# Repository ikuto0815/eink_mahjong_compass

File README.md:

# E-ink mahjong compass

This repo contains all the files neccesary to build a bluetooth controlled digital mahjong compass.

The project is divided into the following main parts:

* [**3d**](3d): the freecad project and stl-files to 3D print the case
* [**android_app**](android_app): the android app used to control the device
* [**firmware**](firmware): firmware for the ESP32 microcontroller inside
* [**pcb**](pcb): design files for the custom PCB

Additional folders:

* [**fontconvert**](fontconvert): tool to convert fonts to C headers, so they can be used in the firmware
* [**hardware**](hardware): datasheets for parts used on the PCB

## PCB

The custom made PCB contains an ESP32-S3-WROOM1 microcontroller to talk to a phone via bluetooth and control the connected periphery.

It has the following components:

* 4.2 inch 400x300 (300x300 visible) E-ink display
* 4 buttons for controlling the device
* 4 indicator LEDs placed below the riichi bet trays of each player
* USB-C port for programming the ESP32 and charging the battery
* TP4056 module to control charging of a single cell LiPo battery via the USB-C port
* (optional and untested MAX17048 fuel gauge controller to determine the battery charge)

The production subfolder contains all the files needed to order the PCBs.
The `eink_mahjong_compass.zip` file contains alle the gerber files needed to order the PCB.
`bom.csv` and `positions.csv` are additionally needed when ordering the PCBs assembled.
The files for assembly will work for JLCPCB, other sites might need a different file format.

Even when ordering with assembly, two parts have to be soldered by hand. Those being the connector
for the E-ink display and the ESP32 module. Adding those would make the assembly service much more expensive.

## How to build

### Requirements

The following things need to be ordered:

* WeAct 4.2 inch Epaper module <https://aliexpress.com/item/1005008461198386.html> (only sold by WeAct Studio Official Store, order the black/white one, the black/red/white variant might not work)
* ESP32-S3-WROOM1-N4 <https://aliexpress.com/item/1005004815894336.html> (there are various vendors, they should all be fine. -N4 is the cheapest variant with 4MB flash and no external RAM. The better variants will probably work as well but won't provide any benefits)
* 2x 4 pin PCB Female Pin Header Socket Connector <https://aliexpress.com/item/1005004122312694.html> for the display connector
* (optional) Ntag 215 NFC tag stickers <https://aliexpress.com/item/1005006387440192.html> stick them on the underside of the lid and write the connect URL to them, so the app auto starts when touching item
* battery, either a 5000mAh 105080 or a 6000mAh 906090 can be used, other formats would need changes to the 3D printed part to hold the battery in place. Example seller <https://aliexpress.com/item/1005004639603622.html> batteries from other sellers will probably work fine as well, but a 2 pin connector is required, not a 3 pin one.
* M3xL4xOD4.2 brass insert nuts. <https://de.aliexpress.com/item/1005006472702418.html> Molded into the case to hold the lid screws
* M3 6mm countersunk screws <https://aliexpress.com/item/33006942612.html>

### Assembly

* 3D print the parts as described in [3d/README](3d/README.md).
* Using a soldering iron push the brass insert nuts into the corners of the case.
* Place the PCB on the printed `display_feet`
* Place the display_feet on top
* Put them into the case
* Place the battery inside and connect it after checking if the polarity of the connector matches that on the PCB.
* Add the screen
* Place the lid on top and screw it down.

### Flashing the firmware

To build and flash the firmware, you need to download and install  [PlatformIO](https://platformio.org/).

Then just connect the compass via USB and run `pio run --target upload` in the firmware directory.

## Other stuff

### Bluetooth interface

The compass currently offers a single BLE service under the UID `bae5e4dd-f2b4-4461-a84c-b7851fb8efd3` with the following characteristics:

#### game state (`bab40271-33ea-48dc-a145-638361f54d2b`)

This characteristic is write only and takes a multi line string that describes the current game state in the following format:

``` text
roundIndex riichiCount honbaCount
windIndex0
score0
name0
windIndex1
score1
name1
windIndex2
score2
name2
windIndex3
score3
name3
```

roundIndex describes the current round of the game (0=E1, 1=E2, 4=S1,...). riichiCount and honbaCount are the number of sticks that would be on the table.

The next lines describe describe the 4 players in the game.
windIndexN is the current wind of each player (0=E, 1=S, 2=W, 3=N).
scoreN and nameN are the current score and name of each player.

The players are drawn on the display in the same order as in the transferred data.

Example:

``` text
1 2 1
0
29000
name0
1
29000
name1
2
38000
name2
3
22000
name3
```

This game is in round east-2, There are two riichi sticks and one honba in the table. Player "name0" is currently east with 29000 points.

#### battery voltage (`bab40271-33ea-48dc-a145-638361f54d2c`)

This characteristic is read-only. It returns the current battery voltage in mV. This can be used for a battery level indicator in the app.

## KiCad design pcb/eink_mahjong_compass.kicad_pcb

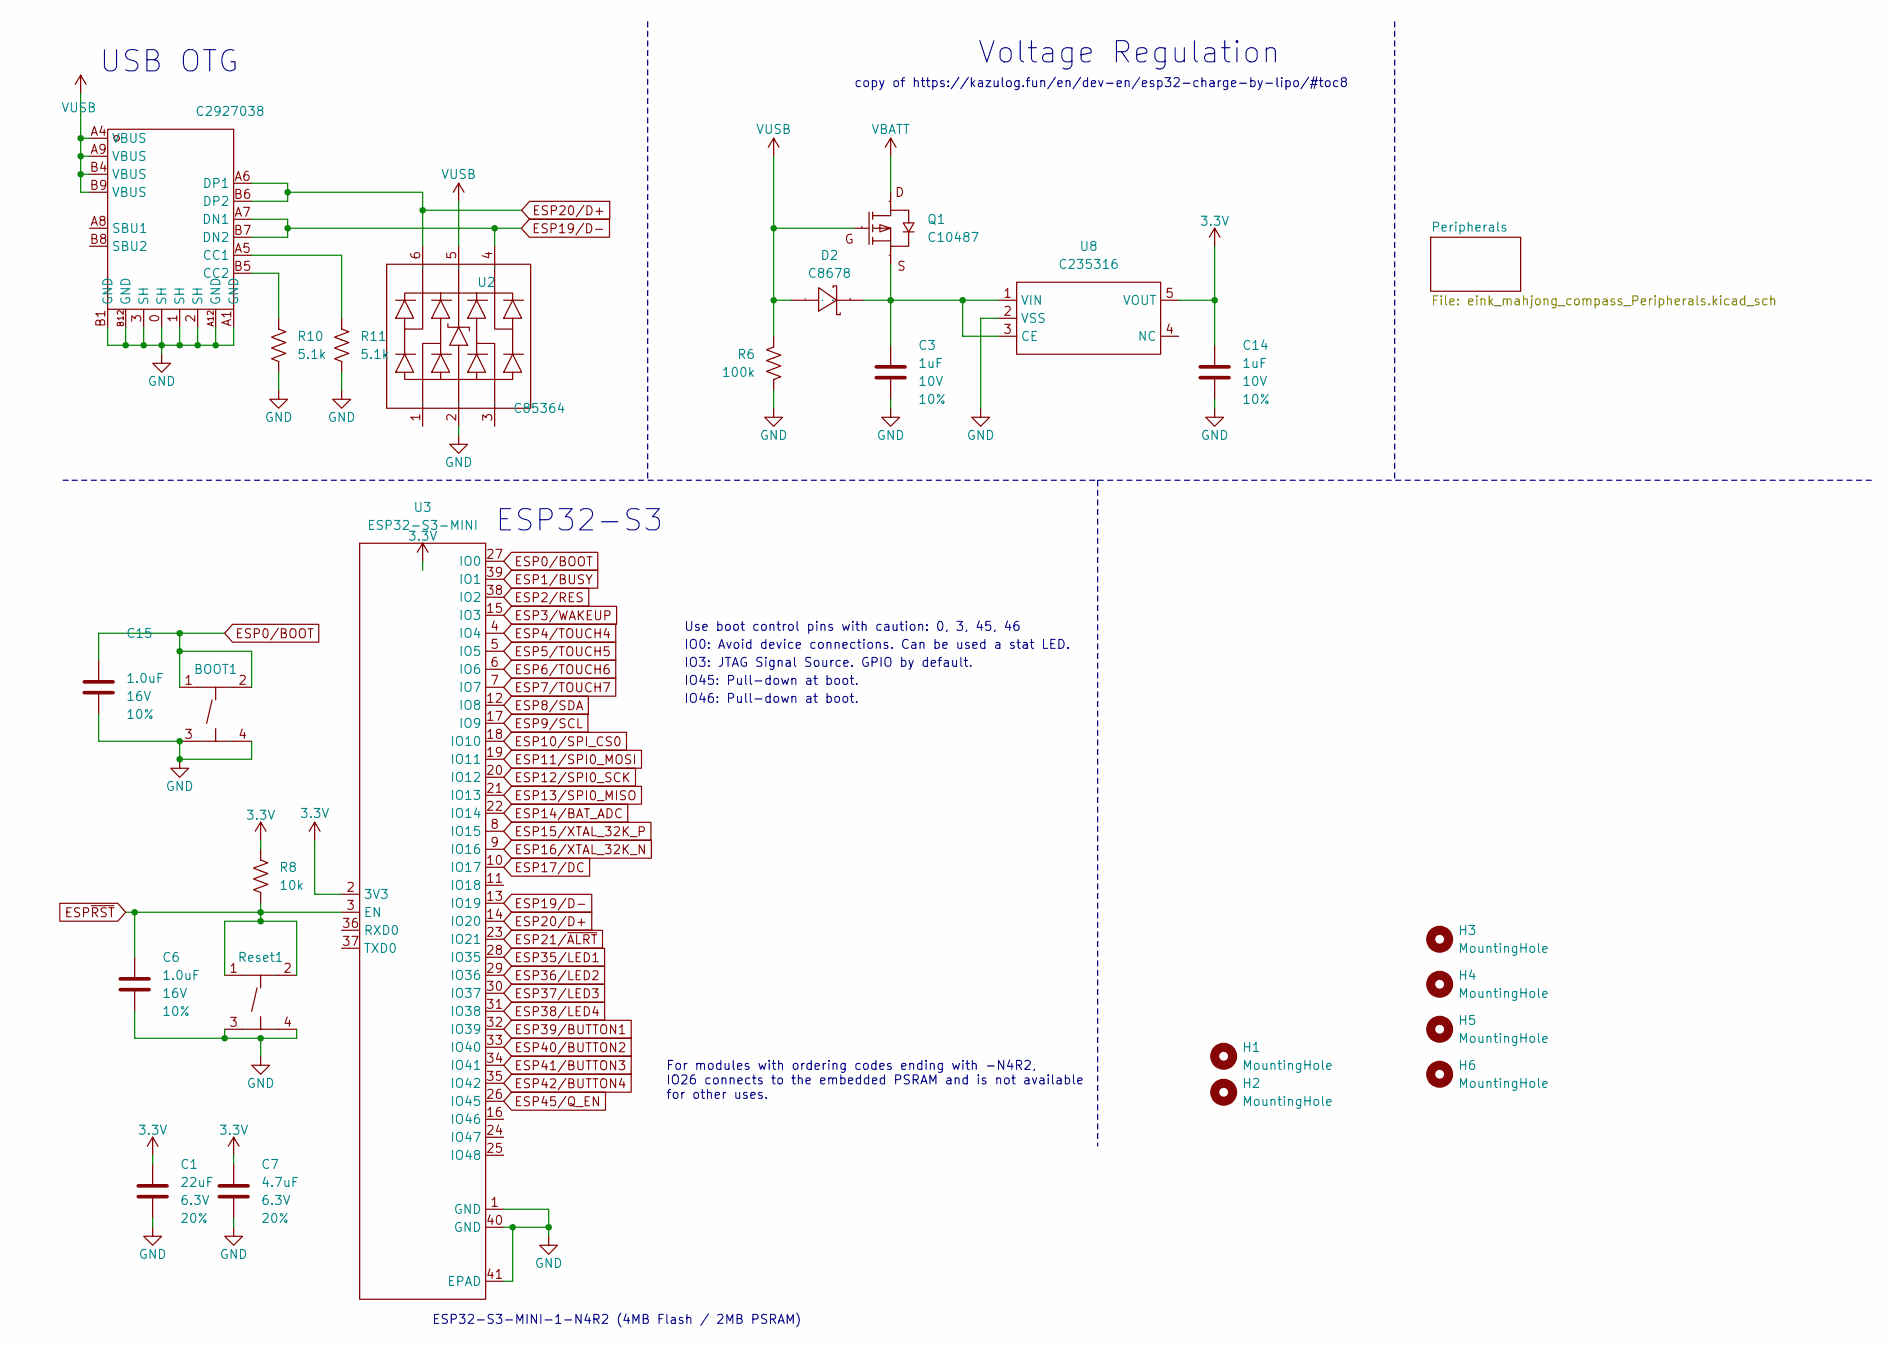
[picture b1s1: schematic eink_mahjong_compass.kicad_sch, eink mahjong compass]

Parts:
BOOT1: C318884; SW-SMD_4P-L5.1-W5.1-P3.70-LS6.5-TL_H1.5; Manufacturer Part TS-1187A-B-A-B; LCSC Part Name 5.1*5.1*1.5mm 立贴 轻触开关
C1: 22uF; C_0603_1608Metric; Voltage 6.3V; Tolerance 20%
C3, C14: 1uF; C_0402_1005Metric; Voltage 10V; Tolerance 10%
C6, C15: 1.0uF; C_0402_1005Metric; Voltage 16V; Tolerance 10%
C7: 4.7uF; C_0402_1005Metric; Voltage 6.3V; Tolerance 20%
D2: C8678; SMA_L4.3-W2.6-LS5.2-RD; Manufacturer Part SS34; LCSC Part Name 电压:40V 电流:3A
H1, H2: MountingHole; MountingHole_6.4mm_M6_DIN965
H3, H4, H5, H6: MountingHole; MountingHole_2.7mm_M2.5_ISO14580
Q1: C10487; SOT-23-3_L3.0-W1.7-P0.95-LS2.9-BR; Manufacturer Part SI2301CDS-T1-GE3; LCSC Part Name 1个P沟道 耐压:20V 电流:3.1A
R6: 100k; R_0402_1005Metric
R8: 10k; R_0402_1005Metric
R10, R11: 5.1k; R_0402_1005Metric
Reset1: C318884; SW-SMD_4P-L5.1-W5.1-P3.70-LS6.5-TL_H1.5; Manufacturer Part TS-1187A-B-A-B; LCSC Part Name 5.1*5.1*1.5mm 立贴 轻触开关
U2: C85364; SOT-23-6_L2.9-W1.6-P0.95-LS2.9-BL; Manufacturer Part C85364; LCSC Part Name 丝印:V05 单向ESD 5V截止 峰值浪涌电流：4A@8/20us
U3: ESP32-S3-MINI; WIRELM-SMD_ESP32-S3-WROOM-1; Manufacturer Part ESP32-S3-WROOM-1; LCSC Part Name ESP32-S3-WROOM-1
U8: C235316; SOT-353_L2.1-W1.3-P0.65-LS2.3-BL; Manufacturer Part ME6211C33R5G; LCSC Part Name 输入6.5V 输出3.3V 300mA
USB2: C2927038; USB-C_SMD-TYPE-C-31-M-12; Manufacturer Part USB-TYPE-C-018; LCSC Part Name Type-C 母 卧贴

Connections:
3.3V: C1.2, C7.1, C14.1, R8.1, U3.2 (3V3), U8.5 (VOUT); also elsewhere on the board
ESP0/BOOT: BOOT1.1 (A), BOOT1.2 (B), C15.1, U3.27 (IO0)
ESP1/BUSY: U3.39 (IO1); also elsewhere on the board
ESP2/RES: U3.38 (IO2); also elsewhere on the board
ESP3/WAKEUP: U3.15 (IO3), U3.35 (IO42); also elsewhere on the board
ESP4/TOUCH4: U3.4 (IO4); also elsewhere on the board
ESP5/TOUCH5: U3.5 (IO5); also elsewhere on the board
ESP6/TOUCH6: U3.6 (IO6); also elsewhere on the board
ESP7/TOUCH7: U3.7 (IO7); also elsewhere on the board
ESP8/SDA: U3.12 (IO8); also elsewhere on the board
ESP9/SCL: U3.17 (IO9); also elsewhere on the board
ESP10/SPI_CS0: U3.18 (IO10); also elsewhere on the board
ESP11/SPI0_MOSI: U3.19 (IO11); also elsewhere on the board
ESP12/SPI0_SCK: U3.20 (IO12); also elsewhere on the board
ESP13/SPI0_MISO: U3.21 (IO13)
ESP14/BAT_ADC: U3.22 (IO14); also elsewhere on the board
ESP15/XTAL_32K_P: U3.8 (IO15); also elsewhere on the board
ESP16/XTAL_32K_N: U3.9 (IO16); also elsewhere on the board
ESP17/DC: U3.10 (IO17); also elsewhere on the board
ESP19/D-: U2.4 (I/O), U3.13 (IO19), USB2.A7 (DN1), USB2.B7 (DN2)
ESP20/D+: U2.6 (I/O), U3.14 (IO20), USB2.A6 (DP1), USB2.B6 (DP2)
ESP21/~ALRT: U3.23 (IO21); also elsewhere on the board
ESP35/LED1: U3.28 (IO35); also elsewhere on the board
ESP36/LED2: U3.29 (IO36); also elsewhere on the board
ESP37/LED3: U3.30 (IO37); also elsewhere on the board
ESP38/LED4: U3.31 (IO38); also elsewhere on the board
ESP39/BUTTON1: U3.32 (IO39); also elsewhere on the board
ESP40/BUTTON2: U3.33 (IO40); also elsewhere on the board
ESP41/BUTTON3: U3.34 (IO41); also elsewhere on the board
ESP45/Q_EN: U3.26 (IO45)
ESP~RST: C6.1, R8.2, Reset1.1 (A), Reset1.2 (B), U3.3 (EN)
GND: BOOT1.3 (C), BOOT1.4 (D), C1.1, C3.2, C6.2, C7.2, C14.2, C15.2, R6.2, R10.1, R11.2, Reset1.3 (C), Reset1.4 (D), U2.2 (VN), U3.1 (GND), U3.40 (GND), U3.41 (EPAD), U8.2 (VSS), USB2.0 (SH), USB2.1 (SH), USB2.2 (SH), USB2.3 (SH), USB2.A1 (GND), USB2.A12 (GND), USB2.B1 (GND), USB2.B12 (GND); also elsewhere on the board
unnamed: C3.1, D2.1 (K), Q1.2 (S), U8.1 (VIN), U8.3 (CE)
unnamed: R11.1, USB2.A5 (CC1)
unnamed: R10.2, USB2.B5 (CC2)
VBATT: Q1.3 (D); also elsewhere on the board
VUSB: D2.2 (A), Q1.1 (G), R6.1, U2.5 (VP), USB2.A4 (VBUS), USB2.A9 (VBUS), USB2.B4 (VBUS), USB2.B9 (VBUS); also elsewhere on the board

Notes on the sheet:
ESP32-S3
copy of https://kazulog.fun/en/dev-en/esp32-charge-by-lipo/#toc8
IO46: Pull-down at boot.
For modules with ordering codes ending with -N4R2, IO26 connects to the embedded PSRAM and is not available for other uses.
IO45: Pull-down at boot.
IO3: JTAG Signal Source. GPIO by default.
USB OTG
ESP32-S3-MINI-1-N4R2 (4MB Flash / 2MB PSRAM)
Voltage Regulation
IO0: Avoid device connections. Can be used a stat LED.
Use boot control pins with caution: 0, 3, 45, 46

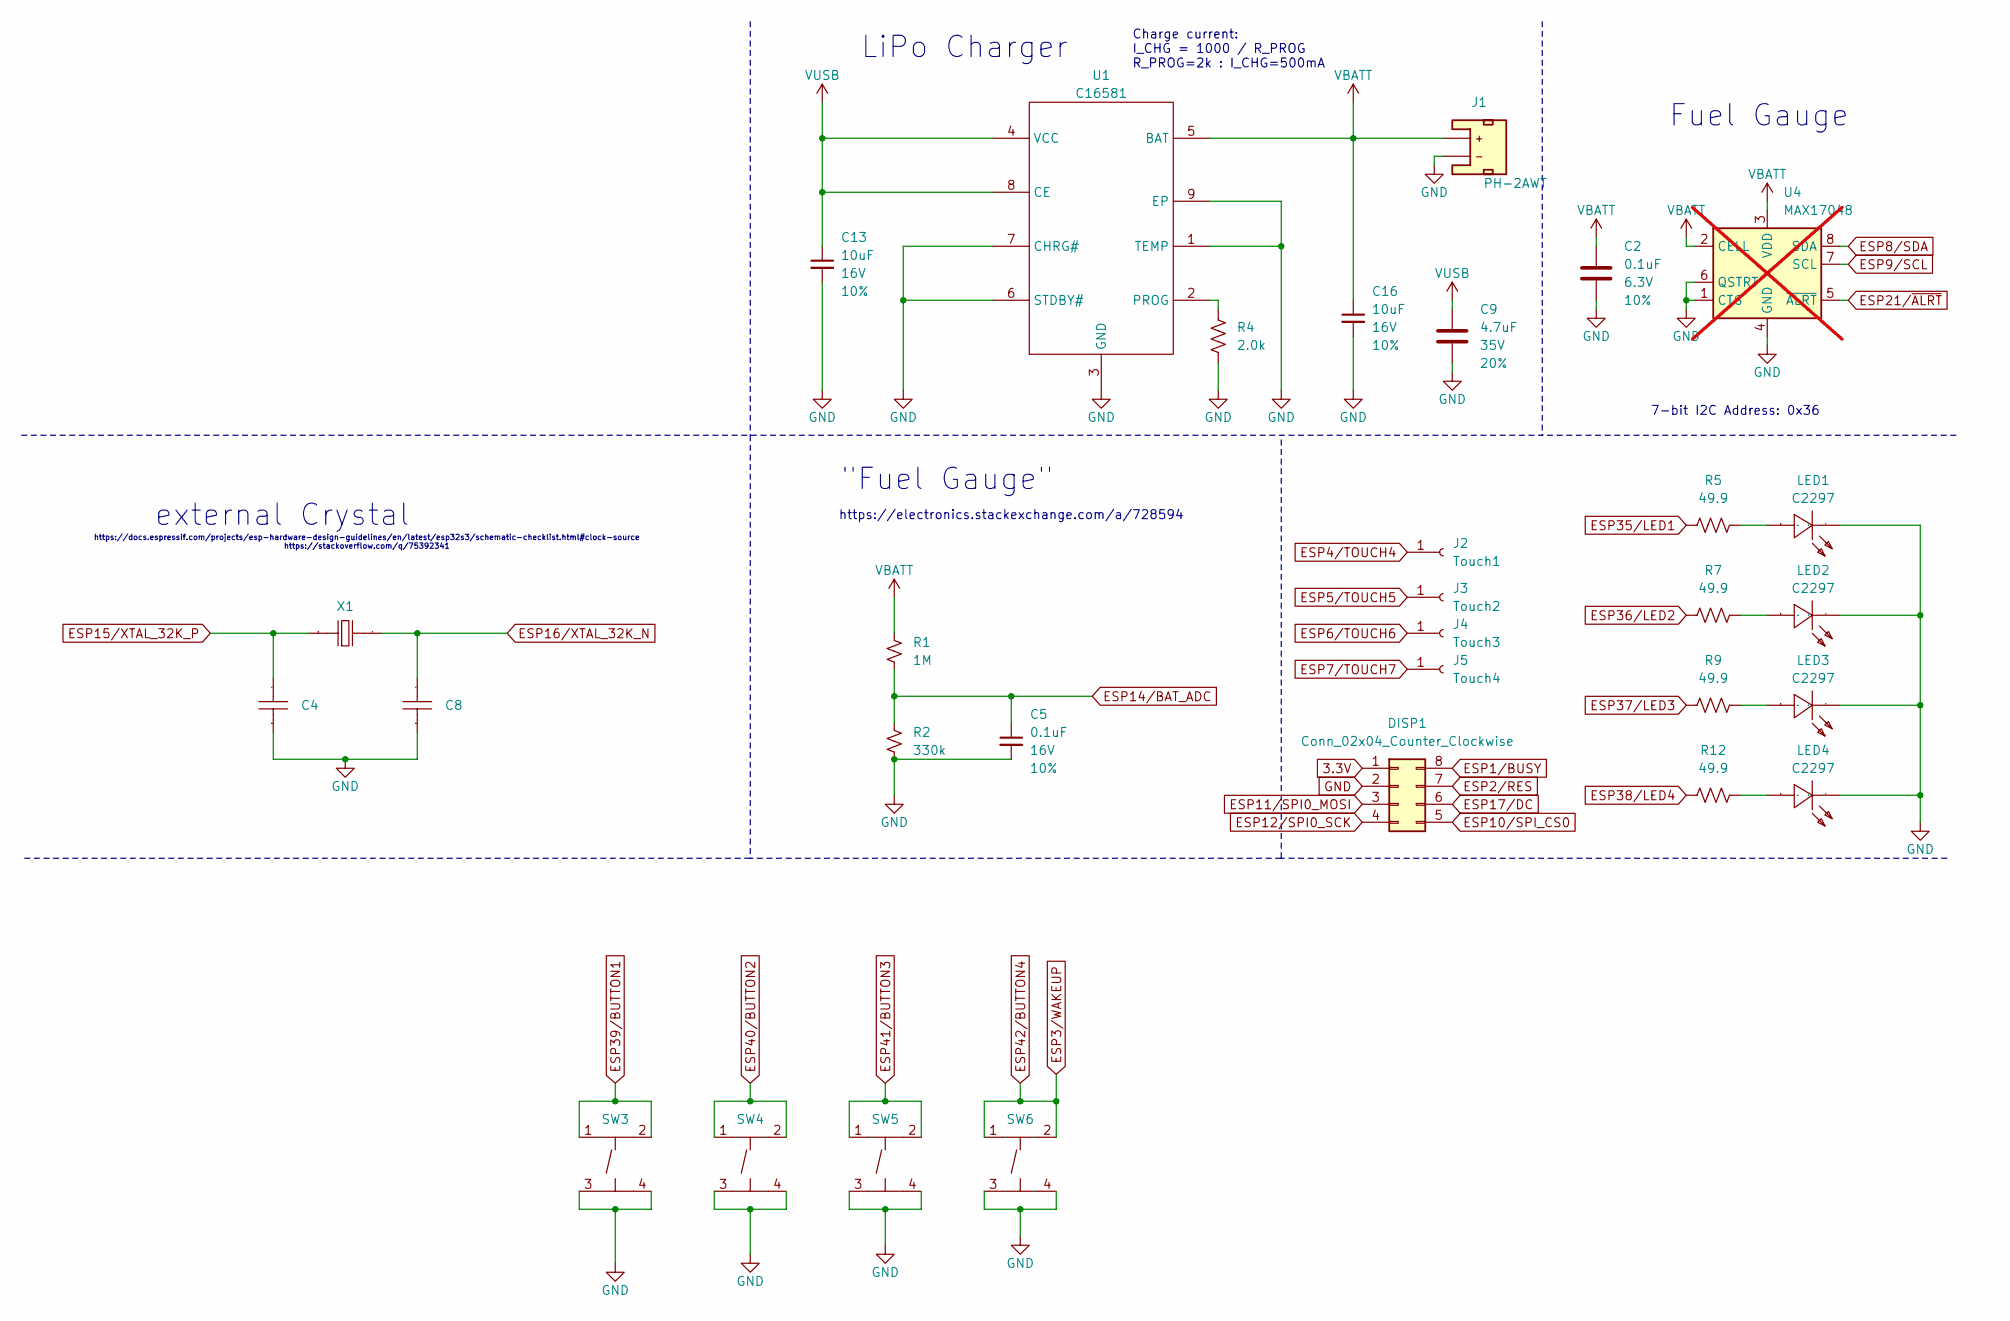
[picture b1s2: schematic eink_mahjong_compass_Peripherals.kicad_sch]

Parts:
C2: 0.1uF; C_0402_1005Metric; Voltage 6.3V; Tolerance 10%
C4, C8: 15pF; C0402; Manufacturer Part 0402CG4R0C500NT; LCSC Part Name ±0.25pF 4pF 50V
C5: 0.1uF; C_0402_1005Metric; Voltage 16V; Tolerance 10%
C9: 4.7uF; C_0402_1005Metric; Voltage 35V; Tolerance 20%
C13, C16: 10uF; C_0402_1005Metric; Voltage 16V; Tolerance 10%
DISP1: Conn_02x04_Counter_Clockwise; PinSocket_2x04_P2.54mm_Vertical
J1: PH-2AWT; CONN-SMD_PH-2AWT; JLC C2763693
J2: Touch1; PinSocket_1x01_P2.54mm_Horizontal
J3: Touch2; PinSocket_1x01_P2.54mm_Horizontal
J4: Touch3; PinSocket_1x01_P2.54mm_Horizontal
J5: Touch4; PinSocket_1x01_P2.54mm_Horizontal
LED1, LED2, LED3, LED4: C2297; LED0805-R-RD; Manufacturer Part KT-0805G; LCSC Part Name 0805 翠绿 高亮
R1: 1M; R_0603_1608Metric
R2: 330k; R_0603_1608Metric
R4: 2.0k; R_0402_1005Metric
R5, R7, R9, R12: 49.9; R_0402_1005Metric
SW3, SW4, SW5, SW6: C318884; SW-SMD_4P-L5.1-W5.1-P3.70-LS6.5-TL_H1.5; Manufacturer Part TS-1187A-B-A-B; LCSC Part Name 5.1*5.1*1.5mm 立贴 轻触开关
U1: C16581; ESOP-8_L4.9-W3.9-P1.27-LS6.0-BL-EP; Manufacturer Part TP4056-42-ESOP8; LCSC Part Name 单节锂离子电池线性充电器
U4: MAX17048; DFN-8; not fitted
X1: C32346; FC-135R_L3.2-W1.5; Manufacturer Part Q13FC13500004; LCSC Part Name 32.768kHz ±20ppm 12.5pF

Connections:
3.3V: DISP1.1; also elsewhere on the board
ESP1/BUSY: DISP1.8; also elsewhere on the board
ESP2/RES: DISP1.7; also elsewhere on the board
ESP3/WAKEUP: SW6.1 (A), SW6.2 (B); also elsewhere on the board
ESP4/TOUCH4: J2.1 (Pin_1_1); also elsewhere on the board
ESP5/TOUCH5: J3.1 (Pin_1_1); also elsewhere on the board
ESP6/TOUCH6: J4.1 (Pin_1_1); also elsewhere on the board
ESP7/TOUCH7: J5.1 (Pin_1_1); also elsewhere on the board
ESP8/SDA: U4.8 (SDA); also elsewhere on the board
ESP9/SCL: U4.7 (SCL); also elsewhere on the board
ESP10/SPI_CS0: DISP1.5; also elsewhere on the board
ESP11/SPI0_MOSI: DISP1.3; also elsewhere on the board
ESP12/SPI0_SCK: DISP1.4; also elsewhere on the board
ESP14/BAT_ADC: C5.1, R1.1, R2.2; also elsewhere on the board
ESP15/XTAL_32K_P: C4.2, X1.1; also elsewhere on the board
ESP16/XTAL_32K_N: C8.2, X1.2; also elsewhere on the board
ESP17/DC: DISP1.6; also elsewhere on the board
ESP21/~ALRT: U4.5 (~ALRT); also elsewhere on the board
ESP35/LED1: R5.1; also elsewhere on the board
ESP36/LED2: R7.1; also elsewhere on the board
ESP37/LED3: R9.1; also elsewhere on the board
ESP38/LED4: R12.1; also elsewhere on the board
ESP39/BUTTON1: SW3.1 (A), SW3.2 (B); also elsewhere on the board
ESP40/BUTTON2: SW4.1 (A), SW4.2 (B); also elsewhere on the board
ESP41/BUTTON3: SW5.1 (A), SW5.2 (B); also elsewhere on the board
GND: C2.2, C4.1, C5.2, C8.1, C9.2, C13.2, C16.2, DISP1.2, J1.1 (-), LED1.2 (K), LED2.2 (K), LED3.2 (K), LED4.2 (K), R2.1, R4.2, SW3.3 (C), SW3.4 (D), SW4.3 (C), SW4.4 (D), SW5.3 (C), SW5.4 (D), SW6.3 (C), SW6.4 (D), U1.1 (TEMP), U1.3 (GND), U1.6 (STDBY#), U1.7 (CHRG#), U1.9 (EP), U4.1 (CTG), U4.4 (GND), U4.6 (QSTRT), U4.9 (GND); also elsewhere on the board
unnamed: LED1.1 (A), R5.2
unnamed: LED2.1 (A), R7.2
unnamed: LED3.1 (A), R9.2
unnamed: LED4.1 (A), R12.2
unnamed: R4.1, U1.2 (PROG)
VBATT: C2.1, C16.1, J1.2 (+), R1.2, U1.5 (BAT), U4.2 (CELL), U4.3 (VDD); also elsewhere on the board
VUSB: C9.1, C13.1, U1.4 (VCC), U1.8 (CE); also elsewhere on the board

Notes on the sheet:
https://docs.espressif.com/projects/esp-hardware-design-guidelines/en/latest/esp32s3/schematic-checklist.html#clock-source https://stackoverflow.com/q/75392341
LiPo Charger
Charge current: I_CHG = 1000 / R_PROG R_PROG=2k : I_CHG=500mA
Fuel Gauge
external Crystal
https://electronics.stackexchange.com/a/728594
"Fuel Gauge"
7-bit I2C Address: 0x36

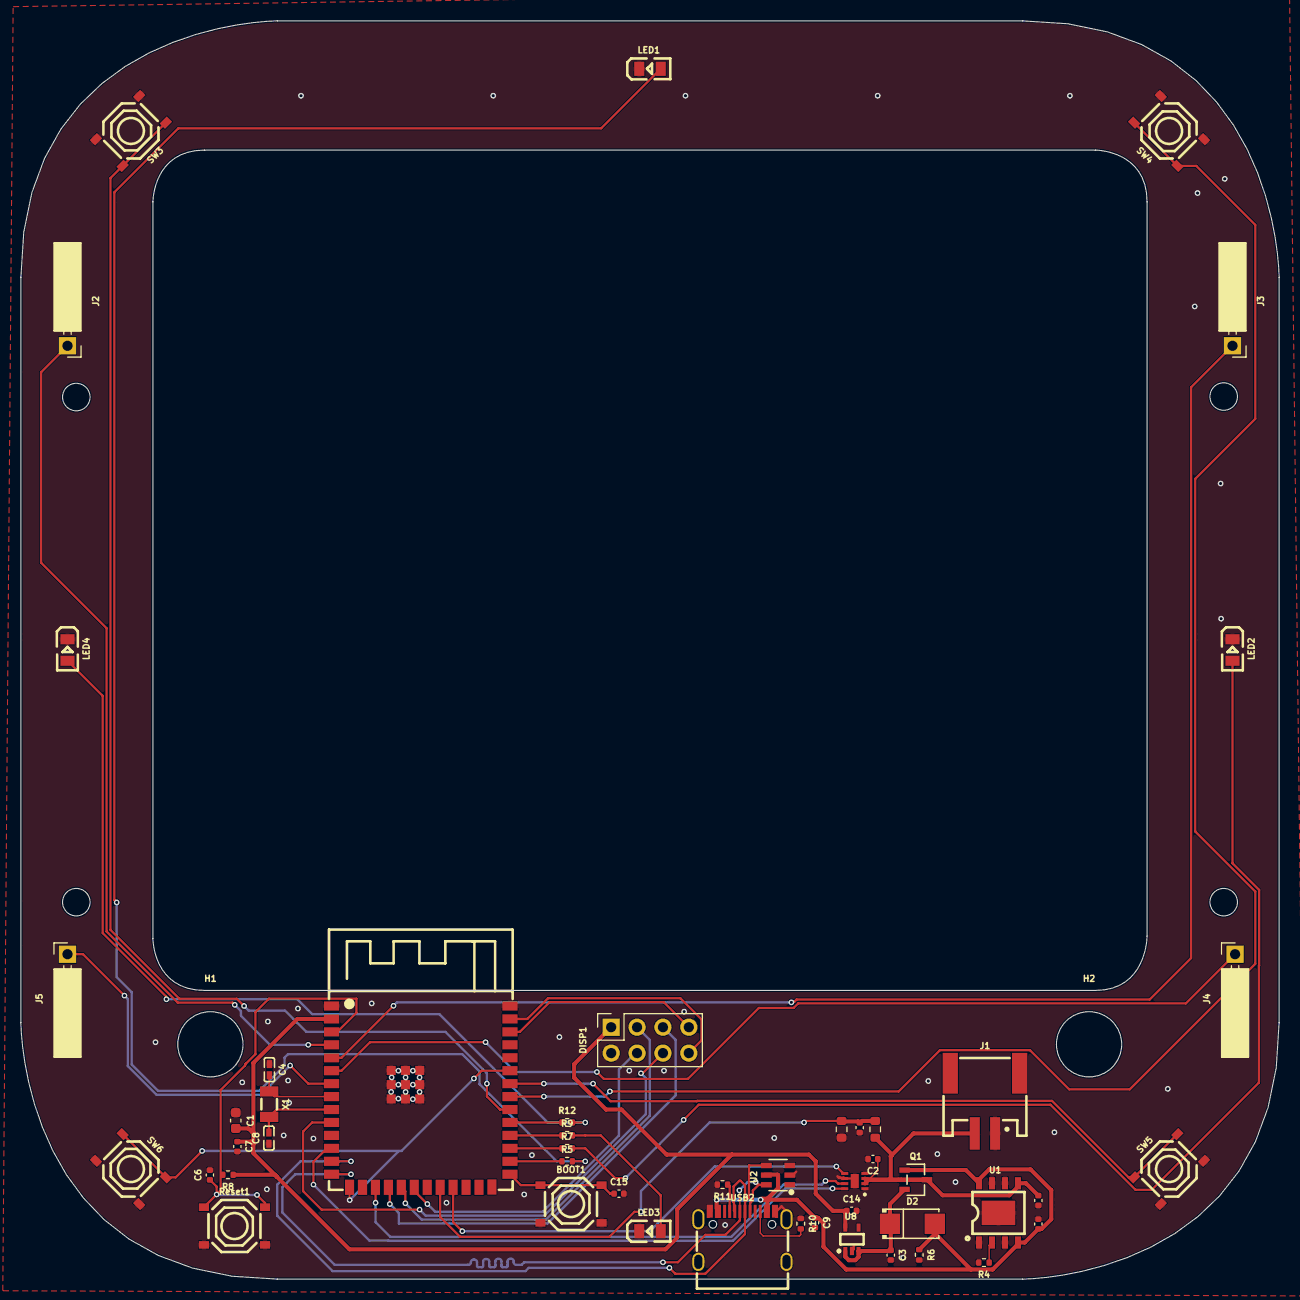
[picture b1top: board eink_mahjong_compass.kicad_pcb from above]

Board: 2 copper layers, 123.4 x 123.4 mm, 55 parts (0 on the bottom side), 40 nets.

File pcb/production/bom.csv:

Designator,Footprint,Quantity,Value,LCSC Part #
"BOOT1, RESET1, SW3, SW4, SW5, SW6",SW-SMD_4P-L5.1-W5.1-P3.70-LS6.5-TL_H1.5,6,C318884,
C1,0603,1,22uF,
"C13, C16",0402,2,10uF,
"C14, C3",0402,2,1uF,
"C15, C6",0402,2,1.0uF,
"C2, C5",0402,2,0.1uF,
"C4, C8",C0402,2,15pF,
"C7, C9",0402,2,4.7uF,
D2,SMA_L4.3-W2.6-LS5.2-RD,1,C8678,
DISP1,PinSocket_2x04_P2.54mm_Vertical,1,Conn_02x04_Counter_Clockwise,
J1,CONN-SMD_PH-2AWT,1,PH-2AWT,C2763693
"LED1, LED2, LED3, LED4",LED0805-R-RD,4,C2297,
Q1,SOT-23-3_L3.0-W1.7-P0.95-LS2.9-BR,1,C10487,
R1,0603,1,1M,
"R10, R11",0402,2,5.1k,
"R12, R5, R7, R9",0402,4,49.9,
R2,0603,1,330k,
R4,0402,1,2.0k,
R6,0402,1,100k,
R8,0402,1,10k,
U1,ESOP-8_L4.9-W3.9-P1.27-LS6.0-BL-EP,1,C16581,
U2,SOT-23-6_L2.9-W1.6-P0.95-LS2.9-BL,1,C85364,
U8,SOT-353_L2.1-W1.3-P0.65-LS2.3-BL,1,C235316,
USB2,USB-C_SMD-TYPE-C-31-M-12,1,C2927038,
X1,FC-135R_L3.2-W1.5,1,C32346,

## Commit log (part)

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2026-01-18 add fontconvert and m2 fonts
2026-01-18 add license
2026-01-18 use own fork of the espressif32 platform without silly python version restriction
2026-01-18 add game state and update from bt
2026-01-18 update 3d model
2026-01-18 add deep sleep wakeup on gpio3
    The button GPIOs arent usable for deep sleep wake up, need to rewire at
    least one of them to the until now unused GPIO3.
2026-01-18 game_state: tabify
2026-01-18 display: set pins to output
2026-01-18 update battery voltage characteristic every 10s
2026-01-18 add stl files for the individual parts
2026-01-18 add prefix to make QR code actually usable with the app
2026-01-18 update active player in game state
2026-01-18 rotate middle part to the first player
2026-01-18 ble: add battery voltage characteristic
2026-01-18 io: no more camel case functions
2026-01-18 add 3d model
2026-01-18 add need_redraw property to game state
2026-01-18 add pio config
2026-01-18 formatter configs
2026-01-18 check for connected device every 100ms
2026-01-18 add missing partition config
2026-01-18 update main loop
2026-01-18 ble: add debug messages
2026-01-18 add display
2026-01-18 init io
2026-01-18 update GxEPD2 lib
2026-01-18 add function to read the battery voltage
2026-01-18 update gitignore
2026-01-18 combine button and touch handlers
2026-01-18 add LED functions
2026-01-18 add README for 3D stuff
2026-01-18 increase font size for standby message
2026-01-18 rework touch wakeup configuration
2026-01-18 clang format everything
2026-01-18 initial firmware commit
2026-01-18 initial BLE implementation
2026-01-18 add list of datasheets for used parts and add PDFs
2026-01-18 display: remove unnecessary refresh call
2026-01-20 add kicad files used for first production pcbs
2026-01-20 add production files usable for jlcpcb
2026-01-22 initial dummy android app
2026-01-22 global .gitignore
2026-01-22 app: add required permissions and ask for them
2026-01-22 app: add basic handling code for the connect QR codes
2026-01-22 app: ignore release folder
2026-01-22 app: add settings helper class
2026-01-22 app: add bluetooth helper class
2026-01-22 app: add webview extensions
    This handles the injection of javascript into the
    pantheon webUI to send the player data back to android.
2026-01-22 app: initialize Settings object
2026-01-22 app: get device addresss from app link
2026-01-22 app: add webview to home fragment
2026-01-25 firmware: fix rotation and standby mode message
2026-01-26 app: add settings page with status info
2026-01-26 app: rewrite injected javascript
    Use a MutationObserver to get notified about changes in the website state.
    This way we don't have to periodically look for changes.
    Also remove some unneeded parts of the data before sending it back to android.
2026-01-27 app: bt: store connected status
2026-01-27 app: home: reload webview on resume
    This way, the URL can be changed on the settings.
    When the home page is accessed afterwards, the new
    URL will get loaded.
2026-01-27 app: settings: use bt connected property
2026-01-27 app: settings: allow changing the server
    Add radio buttons to switch between the two currently
    supported hosts.
2026-01-27 app: cleanup imports
2026-01-27 app: remove unused assets
2026-01-27 app: enable minify
2026-01-29 app: fix javascript callback
    what was supposed to save a few bytes when
    transferring the state back to android context
    actually destroyed the javascript game state and
    made it impossible to enter scores because all yaku
    were disabled....
2026-01-29 app: disable unused function warning
    copyData is called from javascript context so
    kotlin can't know that the function is actually used.
2026-01-29 app: replace deprecated Handler usage
2026-01-29 app: remove semicolon
2026-01-29 app: cleanup resource files
2026-01-29 app: suppress deprecation warnings in fallback case
2026-01-29 app: fix some lint warnings
2026-01-29 app: cleanup settings fragment
2026-01-29 app: update dependencies
2026-02-01 add some documentation and images
2026-02-01 README: fix link
2026-02-04 app: fix lint error
2026-02-05 app: actually set correct radio button as selected
    This will need a proper implementation if there
    will be more options in the future.
2026-02-05 app: only reload webview if needed
    Always initializing the webview on onresume()
    caused some annoying delays and forwarded the user
    to the menu screen on BMC pantheon.
    Only do the init code when actually needed,
    so if either there is no current URL or
    it is different than the one from the settings.
2026-02-11 README: describe BT interface
2026-02-11 app: prototype to read battery voltage
2026-02-11 app: add a super simple version check
2026-04-29 Revert "use own fork of the espressif32 platform without silly python version restriction"
    This reverts commit fbb83596cec4a11809ee514463cfc2e9135e7847.
2026-05-15 pcb: convert to newer kicad format
2026-05-15 pcb: add locan gitignore file
2026-05-15 pcb: add missing trace to make deep sleep wakeup work
    Connect button 4 for gpio 3 as well, so it can be used to wake up the
    esp32 from deep sleep as the gpios selected for the buttons don't have
    that capability.
    In a future revision this should be redesigned so all buttons can act as
    wakeup trigger.
2026-06-20 3d: recompute
